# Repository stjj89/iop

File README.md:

iop
===

Static analysis tools, sample exploits, and bugdoor discussed in my paper *Interrupt-oriented  
Programming in Microcontrollers: Codeless and Dataless Attacks and Backdoors*

By Samuel J. Tan <samueltan@gmail.com>

Repo organization
------------------
- **asm/**:		MSP430 assembly source code for synthetic IOP exploits  
- **bugdoor/**:   	Patch for TinyOS 2.0 to implant IOP bugdoor  
- **idapython/**: 	IDAPython static analysis scripts  
- **mspdebug/**:  	Patch for mspdebug-0.22 to implement static analysis tools
- **schematics/**: 	Schematics for GoodFET42-JTAG
- **LICENSE**:    	License for using the contents of this repo  
- **README.md**:  	This file

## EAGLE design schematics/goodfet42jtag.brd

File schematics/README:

GoodFET42-JTAG Schematics
====================================
Samuel J. Tan <samueltan@gmail.com>

Description
------------
This are the schematics (.brd and .sch files) for the GoodFET42-JTAG,
a modified GoodFET42 which exposes its JTAG slave and RST/NMI pins.
This board was used for my experiments in my detailed in my interrupt-oriented 
programming paper. These files may be opened with Eagle CAD or a similar tool.

Instructions for preparing board for production
------------------------------------------------
1) Open Eagle CAD
2) Open goodspeed-gerb274x.cam in Eagle's CAM Processor
3) Run the .cam file to produce a set of Gerber files
    > You can view these files in gerbv to see the actual orders that the 
      machines will be processing to make the boards
4) Send the appropriate gerber files to the PCB manufacturer to get the boards 
   made

Bugs
-----
- The MSP430F2618 on the GoodFET42-JTAG currently cannot be properly powered
  over JTAG (USB connection required to power it during JTAG session). The 
  connections from the VCC pin to the MSP430F2618 need to be fixed.

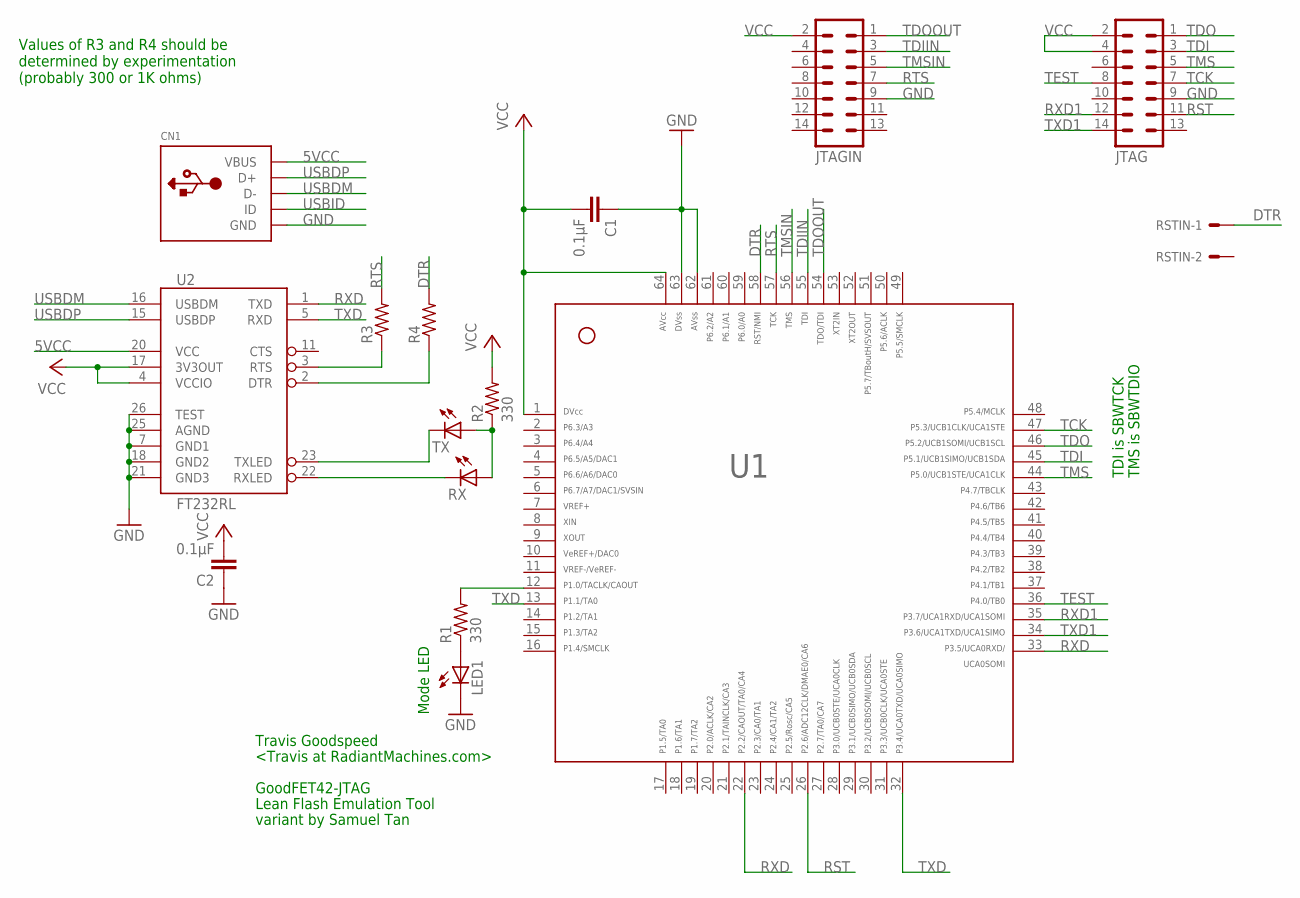
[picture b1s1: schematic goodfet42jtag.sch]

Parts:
C1, C2: 0.1µF; C0603
CN1: USBMINIB; USB-MINIB
JTAG: MA07-2
JTAGIN: MA07-2
LED1: LEDCHIP-LED0603; CHIP-LED0603
R1, R2: 330; R0603
R3, R4: R-US_R0603; R0603
RSTIN: 332-02
RX: LEDCHIP-LED0603; CHIP-LED0603
TX: LEDCHIP-LED0603; CHIP-LED0603
U1: MSP430F2618TPM; PM/PAG64
U2: FT232RL; SSOP28DB

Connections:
5VCC: CN1.VBUS, U2.20 (VCC)
DTR: R4.2, RSTIN.1, U1.58
GND: C1.1, C2.1, CN1.GND, JTAG.9, JTAGIN.9, LED1.C, U1.62, U1.63, U2.7 (GND1), U2.18 (GND2), U2.21 (GND3), U2.25 (AGND), U2.26 (TEST)
unnamed: R1.2, U1.12
unnamed: LED1.A, R1.1
unnamed: R3.1, U2.3 (RTS)
unnamed: R4.1, U2.2 (DTR)
unnamed: RX.C, U2.22 (RXLED)
unnamed: TX.C, U2.23 (TXLED)
unnamed: R2.1, RX.A, TX.A
RST: JTAG.11, U1.26
RTS: JTAGIN.7, R3.2, U1.57
RXD: U1.22, U1.33, U2.1 (TXD)
RXD1: JTAG.12, U1.35
TCK: JTAG.7, U1.47
TDI: JTAG.3, U1.45
TDIIN: JTAGIN.3, U1.55
TDO: JTAG.1, U1.46
TDOOUT: JTAGIN.1, U1.54
TEST: JTAG.8, U1.36
TMS: JTAG.5, U1.44
TMSIN: JTAGIN.5, U1.56
TXD: U1.13, U1.32, U2.5 (RXD)
TXD1: JTAG.14, U1.34
USBDM: CN1.D-, U2.16 (USBDM)
USBDP: CN1.D+, U2.15 (USBDP)
USBID: CN1.ID
VCC: C1.2, C2.2, JTAG.2, JTAG.4, JTAGIN.2, R2.2, U1.1, U1.64, U2.4 (VCCIO), U2.17 (3V3OUT)

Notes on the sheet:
TDI is SBWTCK
TMS is SBWTDIO
Mode LED
Travis Goodspeed
<Travis at RadiantMachines.com>
GoodFET42-JTAG
Lean Flash Emulation Tool
variant by Samuel Tan
Values of R3 and R4 should be determined by experimentation (probably 300 or 1K ohms)

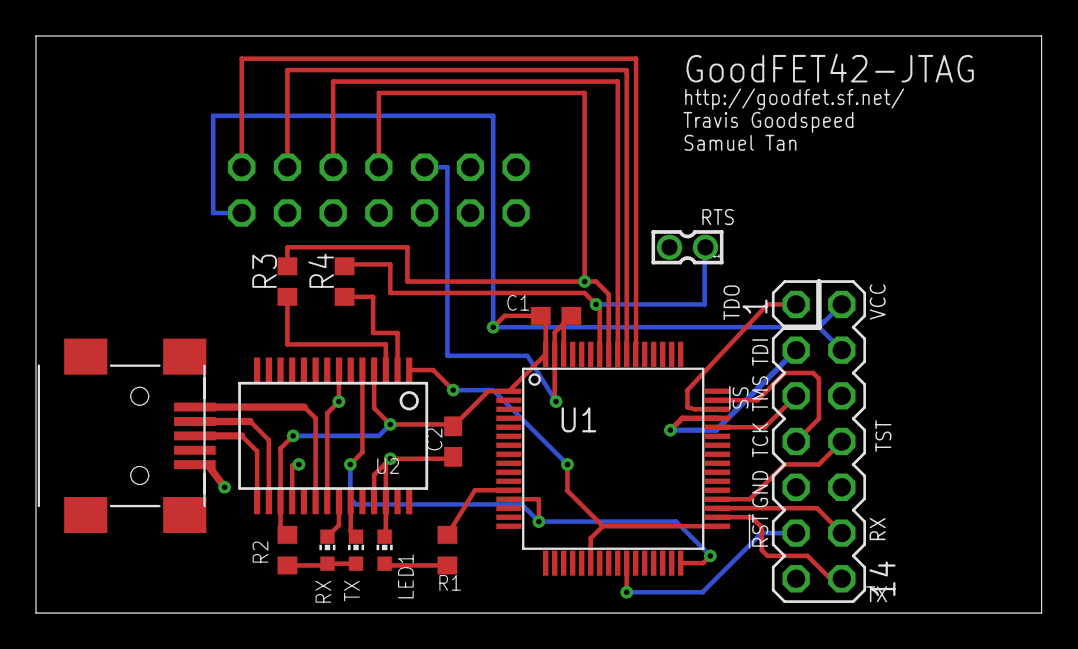
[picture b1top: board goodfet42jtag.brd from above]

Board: 2 copper layers, 55.9 x 32.1 mm, 15 parts (1 on the bottom side), 27 nets.

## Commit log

2014-03-04 Update LICENSE
2014-03-04 Added asm exploit examples and IDAPython scripts
2014-03-04 deleted compiled exploit examples; added .gitignore
2014-03-04 added bugdoor patch
2014-03-05 added mspdebug patch
2014-03-05 added finalized mspdebug patch
2014-03-05 updated patch file
2014-03-10 added GoodFET42-JTAG schematics
2014-03-10 added README and .cam script for producing gerber files
2014-03-10 updated README with schematics/
